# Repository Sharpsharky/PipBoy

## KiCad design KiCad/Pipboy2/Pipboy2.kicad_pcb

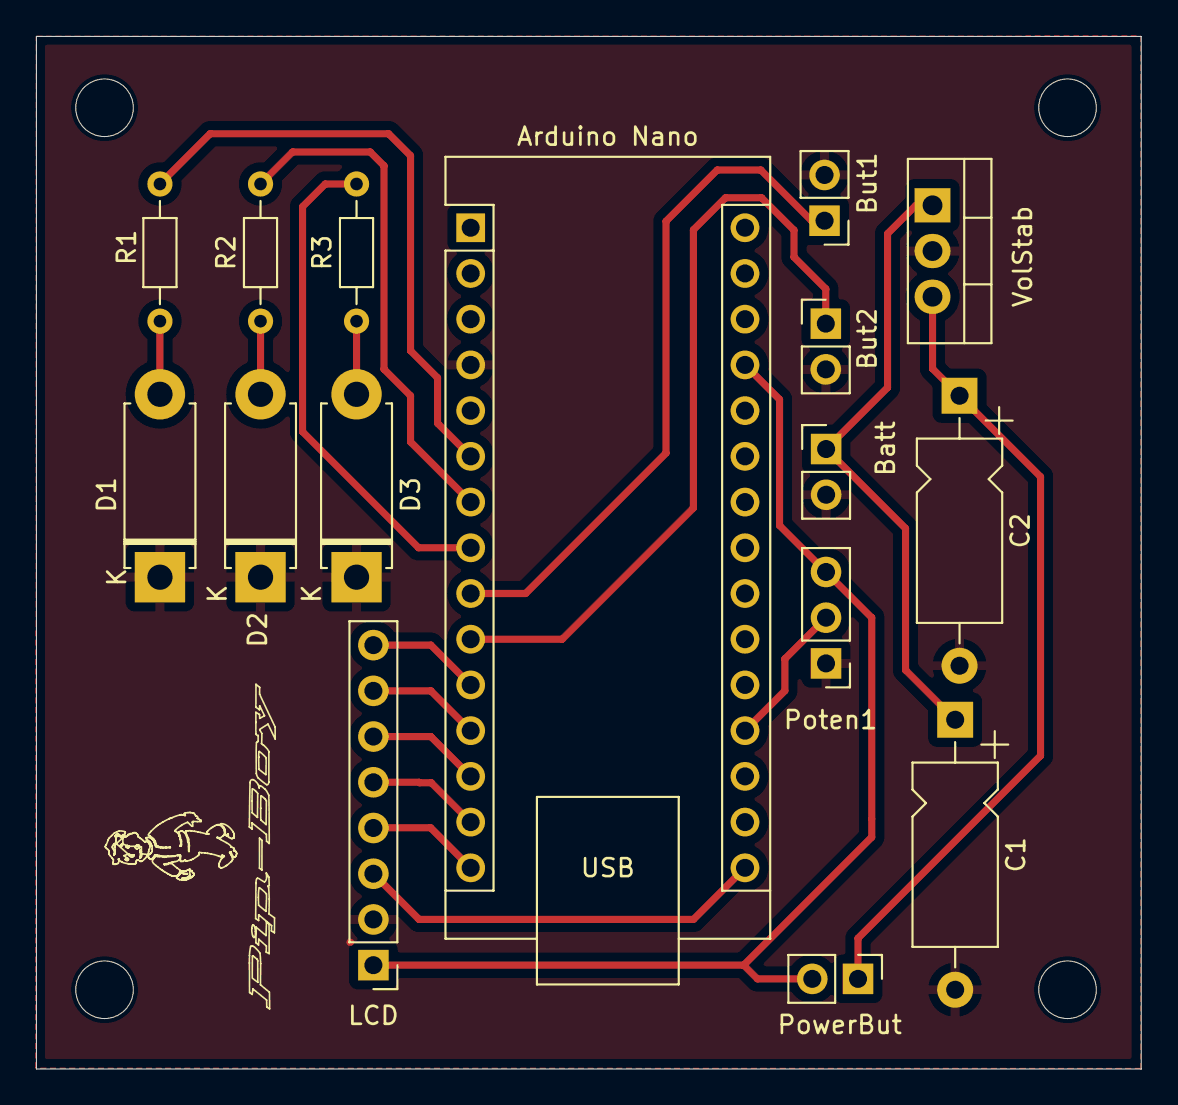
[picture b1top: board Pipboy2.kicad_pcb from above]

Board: 2 copper layers, 61.4 x 57.4 mm, 20 parts (0 on the bottom side), 19 nets.

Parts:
Arduino Nano: Arduino_Nano_v3.x; Arduino_Nano
Batt: Battery Socket; PinHeader_1x02_P2.54mm_Vertical
But1, But2: SW_SPST; PinHeader_1x02_P2.54mm_Vertical
C1: 330nF; CP_Axial_L10.0mm_D4.5mm_P15.00mm_Horizontal
C2: 100nF; CP_Axial_L10.0mm_D4.5mm_P15.00mm_Horizontal
D1, D2, D3: D; D_5W_P10.16mm_Horizontal
H1, H2, H3, H4: MountingHole; MountingHole_3.2mm_M3
LCD: PinHeader_1x08_P2.54mm_Vertical
Poten1: R_Potentiometer; PinHeader_1x03_P2.54mm_Vertical
PowerBut: PinHeader_1x02_P2.54mm_Vertical
R1, R2, R3: 200R; R_Axial_DIN0204_L3.6mm_D1.6mm_P7.62mm_Horizontal
VolStab: L7805; TO-220-3_Vertical

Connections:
GND: Arduino Nano.4 (GND), Batt.2, But1.2 (B), But2.2 (B), C1.2, C2.2, D1.1 (K), D2.1 (K), D3.1 (K), LCD.2, Poten1.1, VolStab.2 (GND)
unnamed: Arduino Nano.19 (A0), Poten1.2
unnamed: Arduino Nano.6 (D3), R1.2
unnamed: Arduino Nano.7 (D4), R2.2
unnamed: Arduino Nano.8 (D5), R3.2
unnamed: Arduino Nano.9 (D6), But1.1 (A)
unnamed: Arduino Nano.10 (D7), But2.1 (A)
unnamed: Arduino Nano.11 (D8), LCD.8
unnamed: Arduino Nano.12 (D9), LCD.7
unnamed: Arduino Nano.13 (D10), LCD.6
unnamed: Arduino Nano.14 (D11), LCD.5
unnamed: Arduino Nano.15 (D12), LCD.4
unnamed: Arduino Nano.16 (D13), LCD.3
unnamed: Batt.1, C1.1, VolStab.1 (IN)
unnamed: D1.2 (A), R1.1
unnamed: D2.2 (A), R2.1
unnamed: D3.2 (A), R3.1
unnamed: C2.1, PowerBut.1, VolStab.3 (OUT)
VCC: Arduino Nano.27 (+5V), LCD.1, Poten1.3, PowerBut.2

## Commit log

2024-09-21 Initialized Arduino Project
2024-09-21 Initialized KiCad Project
2024-09-21 Initialized Inkscape Projects
2024-09-21 Small fix to pcb design, generated gerber files
2024-09-21 Added case maeasurements
2024-10-14 Added voltage reg, power button, updated pcb editor scheme
2024-10-14 Removed plate violations
2024-10-14 Generated gerbers, final pcb polishes
2024-10-22 Exported steps
